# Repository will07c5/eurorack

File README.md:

This an attempt to build various basic analog synthesizer parts in the Eurorack form-factor. It is currently using clones of Curtis Electromusic ICs. Why, you might ask? Mostly just for fun and education.

The circuits are mostly based on the datasheets and various circuits around the web. In particular the triangle to sine conversion in the VCO uses part of Ray Wilson's VCO circuit.

Build at your own risk!

Note that these are currently only partially tested and working.

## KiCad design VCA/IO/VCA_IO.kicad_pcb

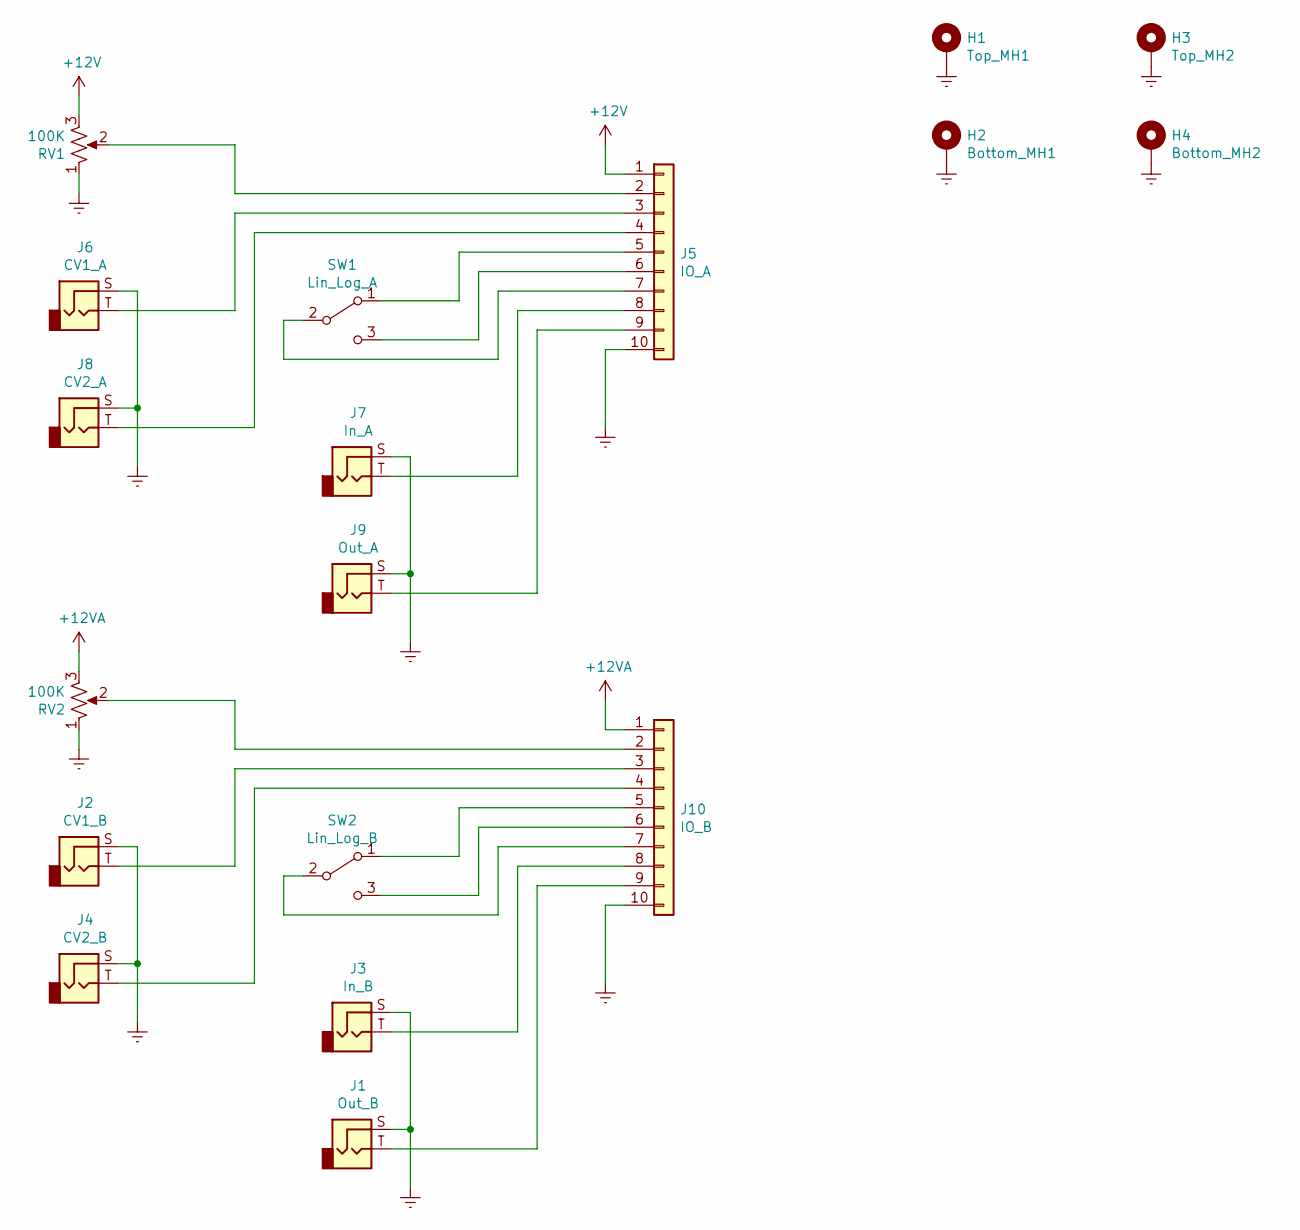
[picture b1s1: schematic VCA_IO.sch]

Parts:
H1: Top_MH1; eurorack_mounting_hole
H2: Bottom_MH1; eurorack_mounting_hole
H3: Top_MH2; eurorack_mounting_hole
H4: Bottom_MH2; eurorack_mounting_hole
J1: Out_B; Jack_3.5mm_QingPu_WQP-PJ398SM_Vertical_CircularHoles
J2: CV1_B; Jack_3.5mm_QingPu_WQP-PJ398SM_Vertical_CircularHoles
J3: In_B; Jack_3.5mm_QingPu_WQP-PJ398SM_Vertical_CircularHoles
J4: CV2_B; Jack_3.5mm_QingPu_WQP-PJ398SM_Vertical_CircularHoles
J5: IO_A; PinSocket_1x10_P2.54mm_Vertical
J6: CV1_A; Jack_3.5mm_QingPu_WQP-PJ398SM_Vertical_CircularHoles
J7: In_A; Jack_3.5mm_QingPu_WQP-PJ398SM_Vertical_CircularHoles
J8: CV2_A; Jack_3.5mm_QingPu_WQP-PJ398SM_Vertical_CircularHoles
J9: Out_A; Jack_3.5mm_QingPu_WQP-PJ398SM_Vertical_CircularHoles
J10: IO_B; PinSocket_1x10_P2.54mm_Vertical
RV1, RV2: 100K; Potentiometer_TT_P0915N
SW1: Lin_Log_A; switch
SW2: Lin_Log_B; switch

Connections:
+12V: J5.1, RV1.3
+12VA: J10.1, RV2.3
GNDREF: H1.1, H2.1, H3.1, H4.1, J1.S, J2.S, J3.S, J4.S, J5.10, J6.S, J7.S, J8.S, J9.S, J10.10, RV1.1, RV2.1
unnamed: J1.T, J10.9
unnamed: J5.2, RV1.2
unnamed: J5.3, J6.T
unnamed: J5.4, J8.T
unnamed: J5.5, SW1.1 (A)
unnamed: J5.6, SW1.3 (C)
unnamed: J5.7, SW1.2 (B)
unnamed: J5.8, J7.T
unnamed: J5.9, J9.T
unnamed: J10.2, RV2.2
unnamed: J2.T, J10.3
unnamed: J4.T, J10.4
unnamed: J10.5, SW2.1 (A)
unnamed: J10.6, SW2.3 (C)
unnamed: J10.7, SW2.2 (B)
unnamed: J3.T, J10.8

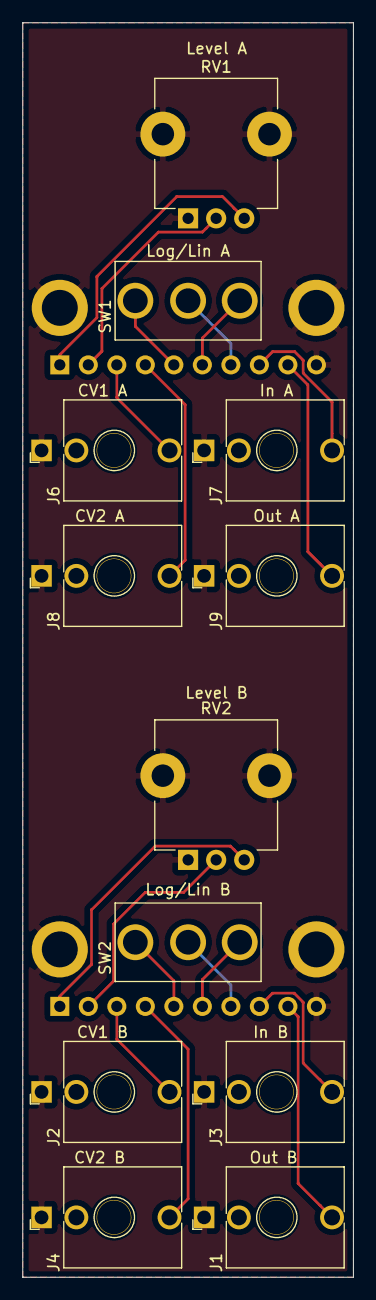
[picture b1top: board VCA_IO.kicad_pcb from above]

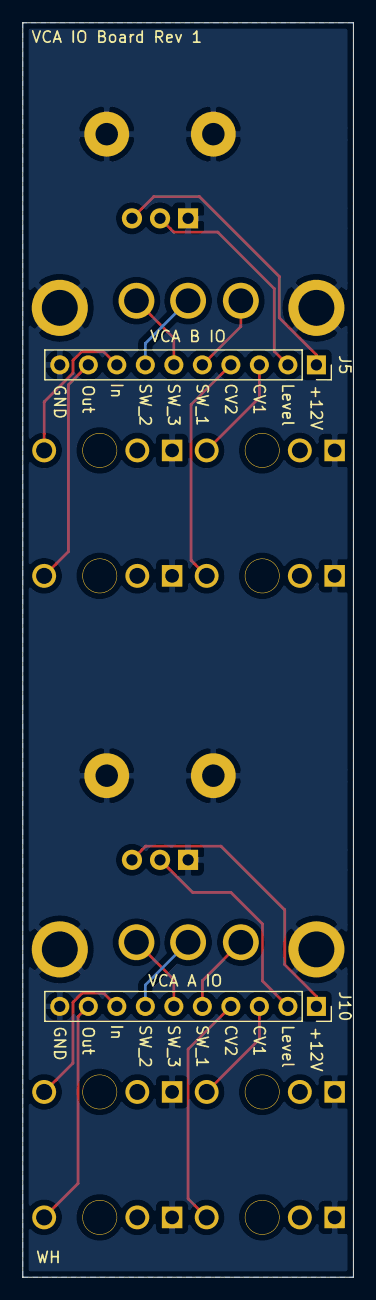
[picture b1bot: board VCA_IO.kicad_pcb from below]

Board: 2 copper layers, 29.5 x 111.8 mm, 18 parts (2 on the bottom side), 19 nets.

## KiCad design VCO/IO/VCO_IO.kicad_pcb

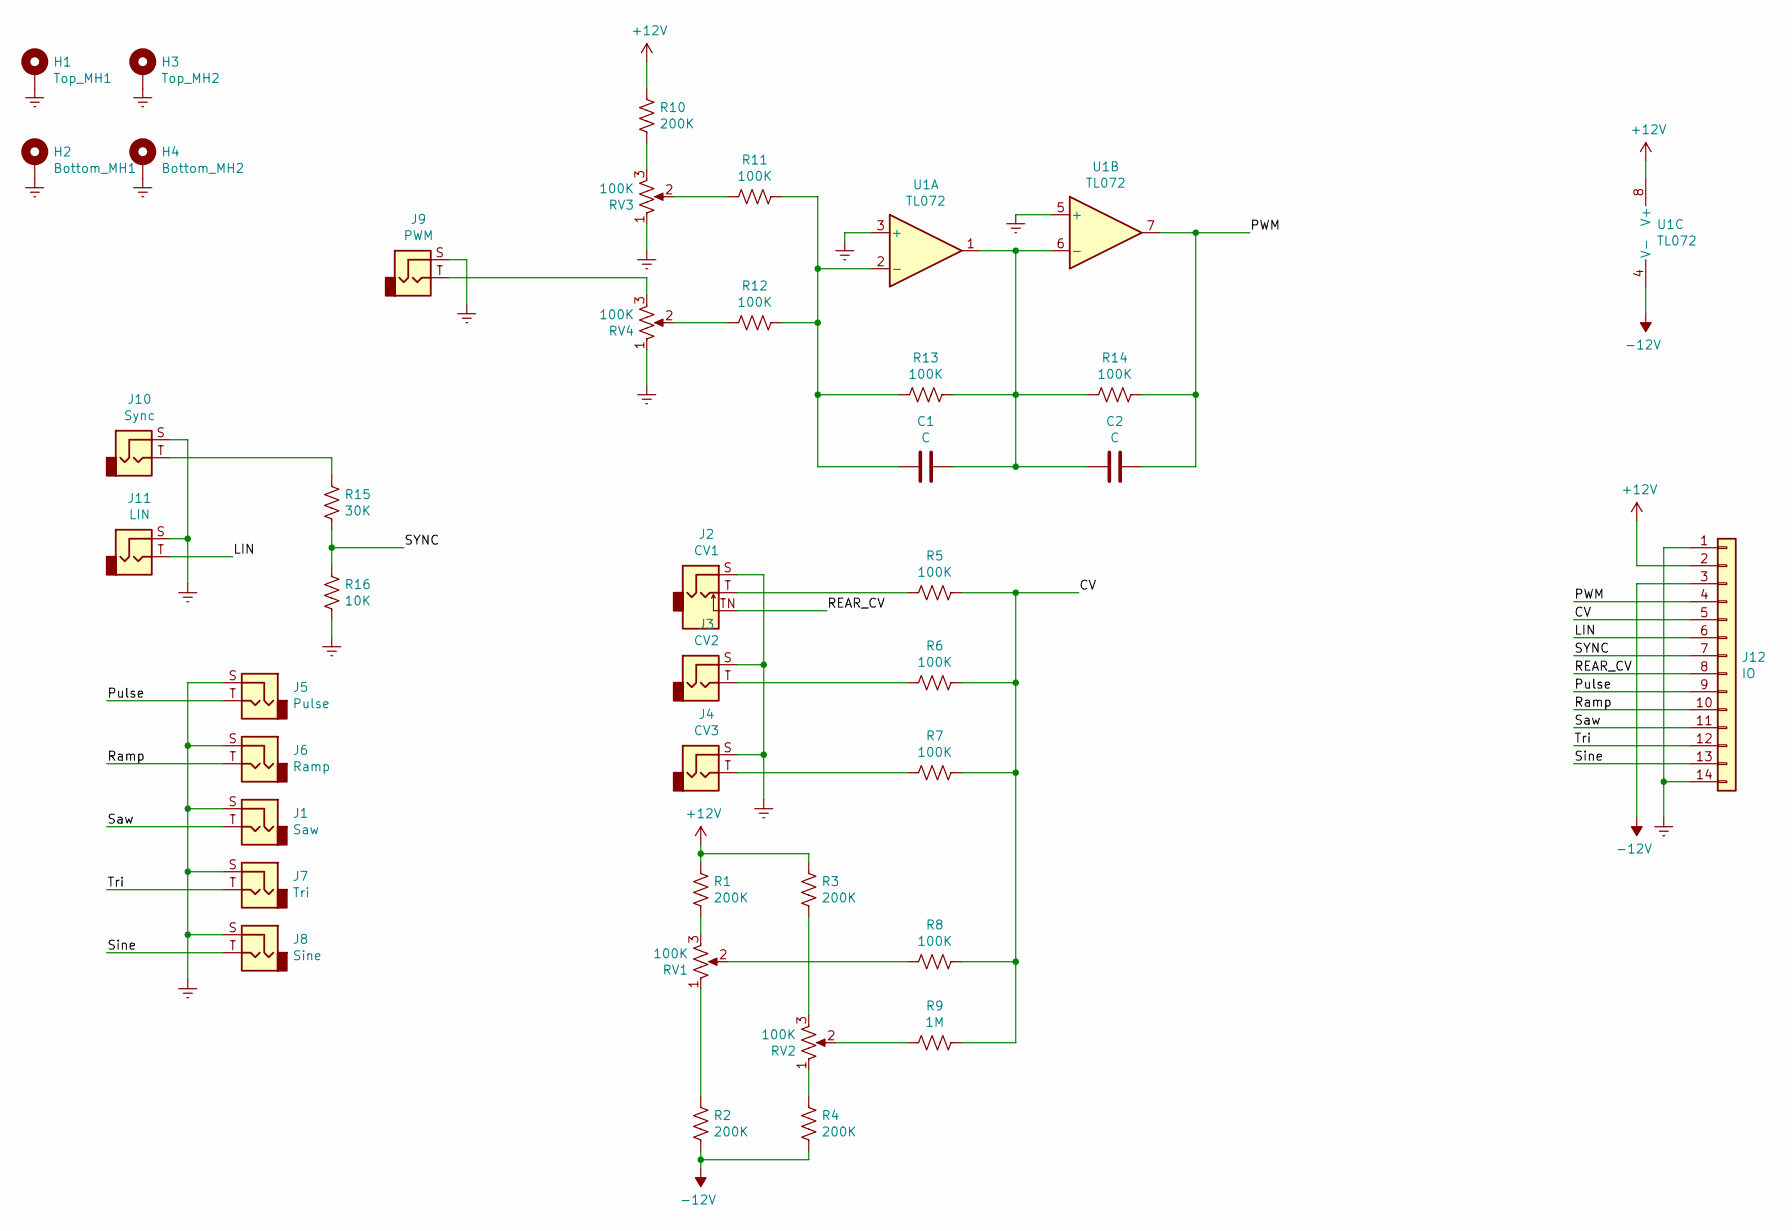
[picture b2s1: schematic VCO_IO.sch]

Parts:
C1, C2: C; C_0805_2012Metric
H1: Top_MH1; eurorack_mounting_hole
H2: Bottom_MH1; eurorack_mounting_hole
H3: Top_MH2; eurorack_mounting_hole
H4: Bottom_MH2; eurorack_mounting_hole
J1: Saw; Jack_3.5mm_QingPu_WQP-PJ398SM_Vertical_CircularHoles
J2: CV1; Jack_3.5mm_QingPu_WQP-PJ398SM_Vertical_CircularHoles
J3: CV2; Jack_3.5mm_QingPu_WQP-PJ398SM_Vertical_CircularHoles
J4: CV3; Jack_3.5mm_QingPu_WQP-PJ398SM_Vertical_CircularHoles
J5: Pulse; Jack_3.5mm_QingPu_WQP-PJ398SM_Vertical_CircularHoles
J6: Ramp; Jack_3.5mm_QingPu_WQP-PJ398SM_Vertical_CircularHoles
J7: Tri; Jack_3.5mm_QingPu_WQP-PJ398SM_Vertical_CircularHoles
J8: Sine; Jack_3.5mm_QingPu_WQP-PJ398SM_Vertical_CircularHoles
J9: PWM; Jack_3.5mm_QingPu_WQP-PJ398SM_Vertical_CircularHoles
J10: Sync; Jack_3.5mm_QingPu_WQP-PJ398SM_Vertical_CircularHoles
J11: LIN; Jack_3.5mm_QingPu_WQP-PJ398SM_Vertical_CircularHoles
J12: IO; PinSocket_1x14_P2.54mm_Vertical
R1, R2, R3, R4, R10: 200K; R_0805_2012Metric
R5, R6, R7, R8, R11, R12, R13, R14: 100K; R_0805_2012Metric
R9: 1M; R_0805_2012Metric
R15: 30K; R_0805_2012Metric
R16: 10K; R_0805_2012Metric
RV1, RV2, RV3, RV4: 100K; Potentiometer_TT_P0915N
U1: TL072; DIP-8_W7.62mm

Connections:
+12V: J12.2, R1.1, R3.1, R10.1, U1.8 (V+)
-12V: J12.3, R2.2, R4.2, U1.4 (V-)
/CV: J12.5, R5.1, R6.1, R7.1, R8.1, R9.1
/LIN: J11.T, J12.6
/PWM: C2.1, J12.4, R14.1, U1.7
/Pulse: J5.T, J12.9
/REAR_CV: J2.TN, J12.8
/Ramp: J6.T, J12.10
/SYNC: J12.7, R15.2, R16.1
/Saw: J1.T, J12.11
/Sine: J8.T, J12.13
/Tri: J7.T, J12.12
GNDREF: H1.1, H2.1, H3.1, H4.1, J1.S, J2.S, J3.S, J4.S, J5.S, J6.S, J7.S, J8.S, J9.S, J10.S, J11.S, J12.1, J12.14, R16.2, RV3.1, RV4.1, U1.3 (+), U1.5 (+)
unnamed: C1.1, C2.2, R13.1, R14.2, U1.1, U1.6 (-)
unnamed: C1.2, R11.1, R12.1, R13.2, U1.2 (-)
unnamed: J2.T, R5.2
unnamed: J3.T, R6.2
unnamed: J4.T, R7.2
unnamed: J9.T, RV4.3
unnamed: J10.T, R15.1
unnamed: R1.2, RV1.3
unnamed: R2.1, RV1.1
unnamed: R3.2, RV2.3
unnamed: R4.1, RV2.1
unnamed: R8.2, RV1.2
unnamed: R9.2, RV2.2
unnamed: R10.2, RV3.3
unnamed: R11.2, RV3.2
unnamed: R12.2, RV4.2

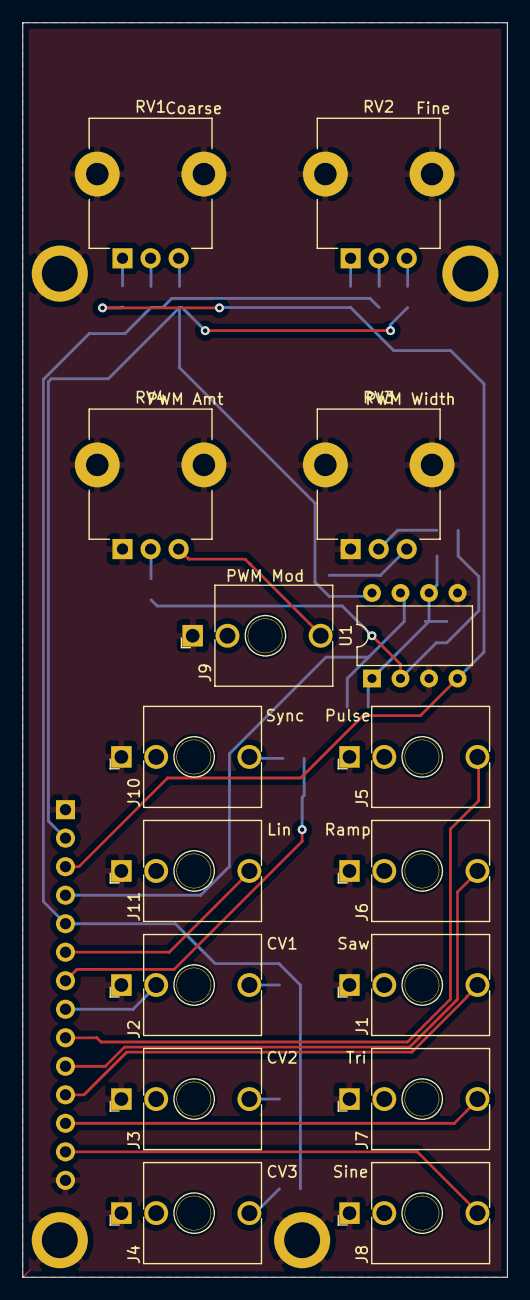
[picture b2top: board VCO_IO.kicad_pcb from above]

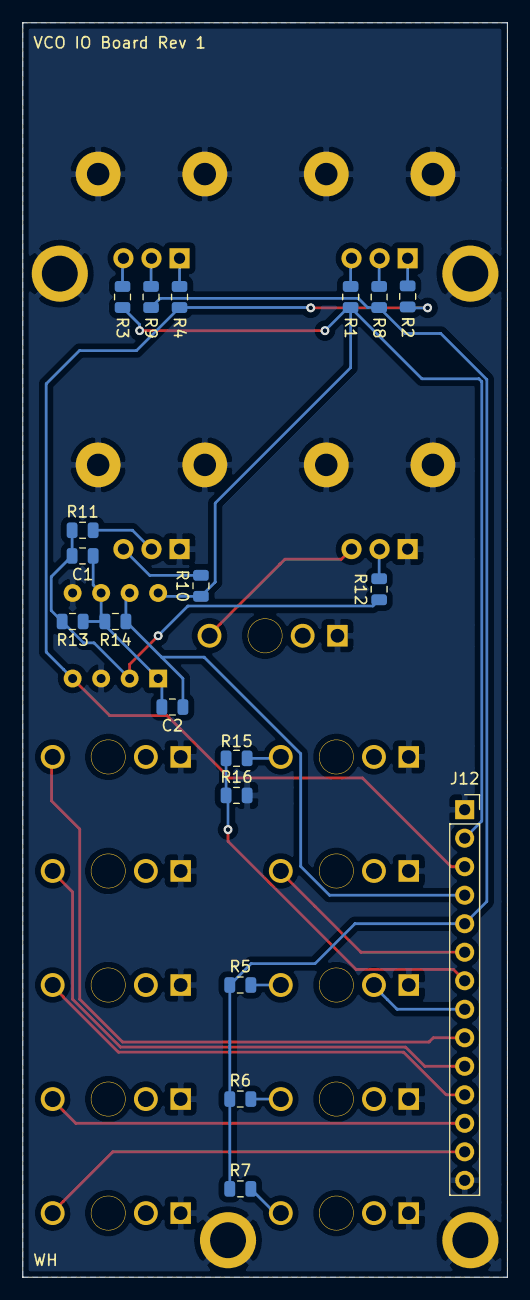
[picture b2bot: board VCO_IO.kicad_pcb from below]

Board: 2 copper layers, 43.2 x 111.8 mm, 39 parts (19 on the bottom side), 29 nets.

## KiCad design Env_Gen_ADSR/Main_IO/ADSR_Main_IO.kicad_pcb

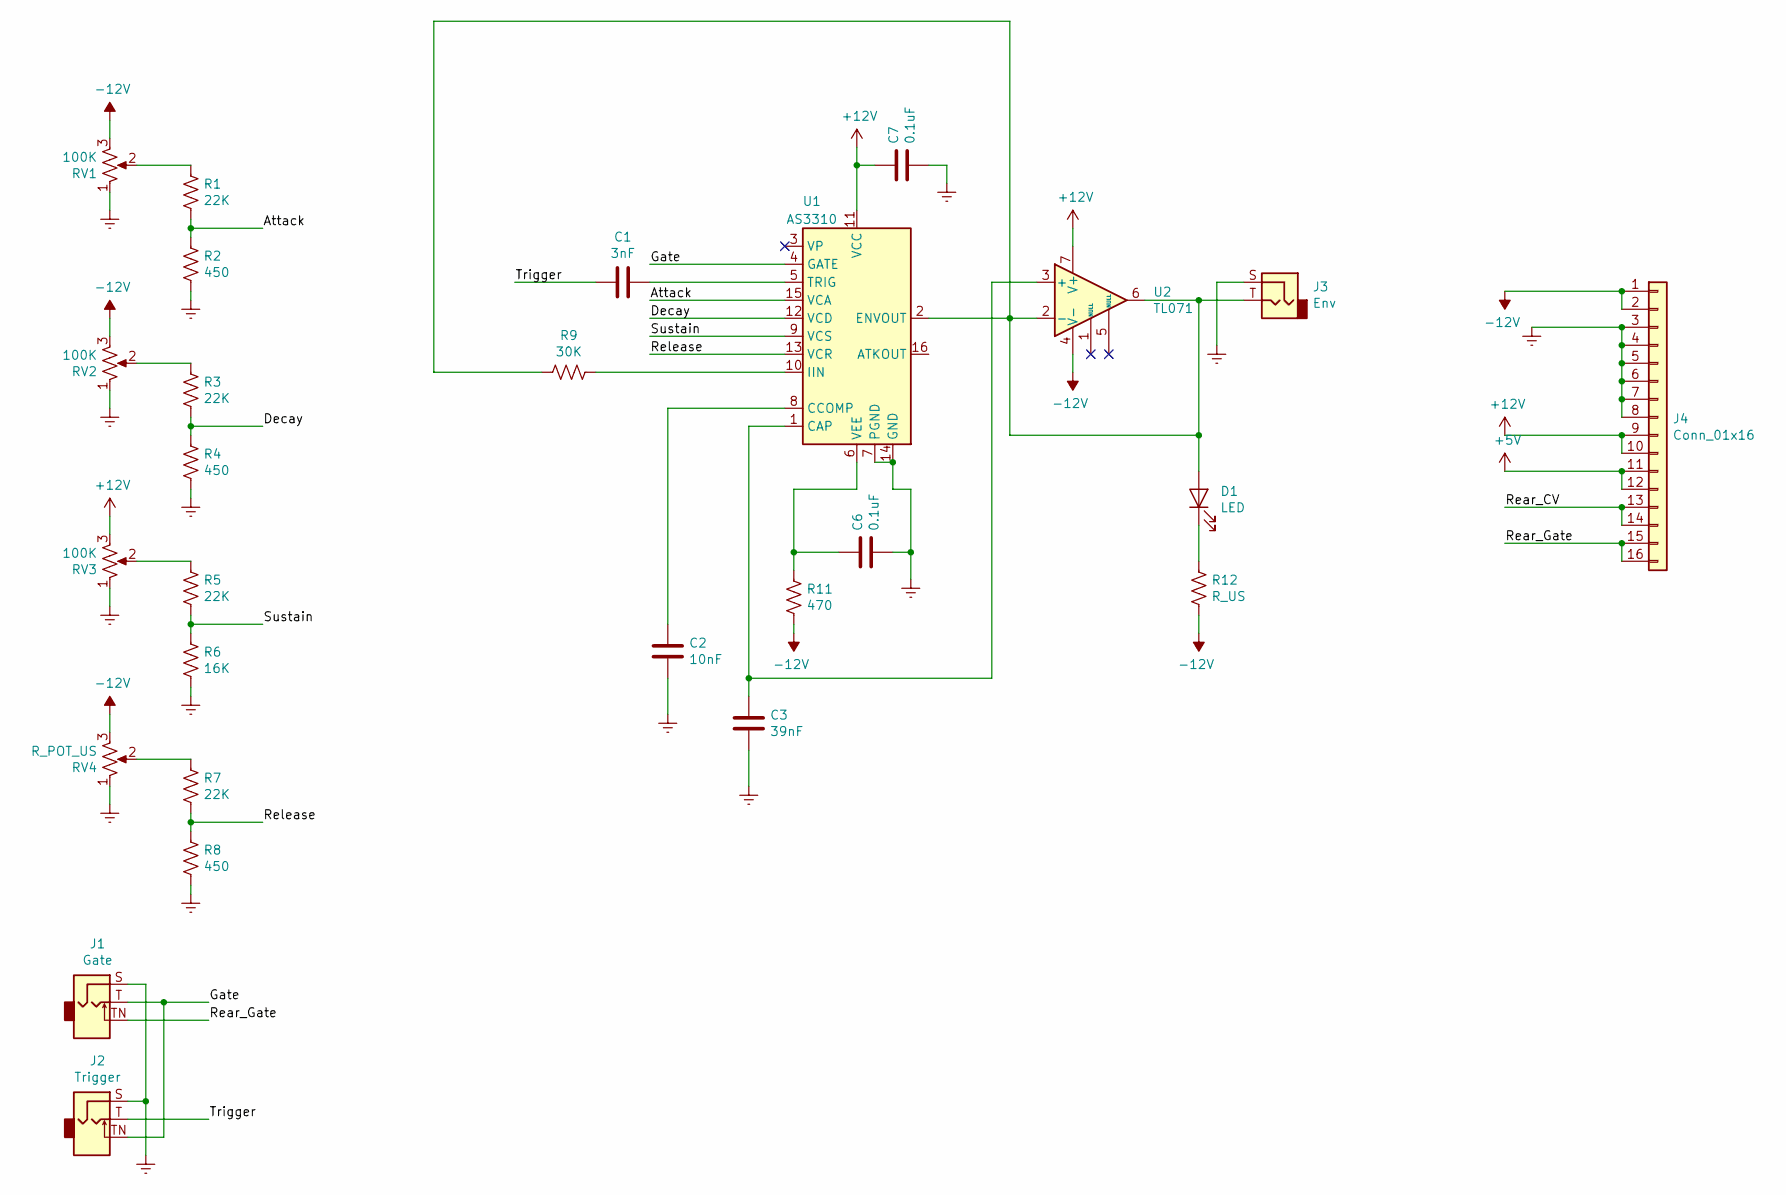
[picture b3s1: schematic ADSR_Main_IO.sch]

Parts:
C1: 3nF; C_0805_2012Metric
C2: 10nF; C_0805_2012Metric
C3: 39nF; C_0805_2012Metric
C6, C7: 0.1uF; C_0805_2012Metric
D1: LED; LED_D5.0mm
J1: Gate; Jack_3.5mm_QingPu_WQP-PJ398SM_Vertical_CircularHoles
J2: Trigger; Jack_3.5mm_QingPu_WQP-PJ398SM_Vertical_CircularHoles
J3: Env; Jack_3.5mm_QingPu_WQP-PJ398SM_Vertical_CircularHoles
J4: Conn_01x16; IDC-Header_2x08_P2.54mm_Vertical
R1, R3, R5, R7: 22K; R_0805_2012Metric
R2, R4, R8: 450; R_0805_2012Metric
R6: 16K; R_0805_2012Metric
R9: 30K; R_0805_2012Metric
R11: 470; R_0805_2012Metric
R12: R_US; R_0805_2012Metric
RV1, RV2, RV3: 100K; Potentiometer_TT_P0915N
RV4: R_POT_US; Potentiometer_TT_P0915N
U1: AS3310; DIP-16_W7.62mm
U2: TL071; DIP-8_W7.62mm

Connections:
+5V: J4.11, J4.12
+12V: C7.1, J4.9, J4.10, RV3.3, U1.11 (VCC), U2.7 (V+)
-12V: J4.1, J4.2, R11.2, R12.2, RV1.3, RV2.3, RV4.3, U2.4 (V-)
/Attack: R1.2, R2.1, U1.15 (VCA)
/Decay: R3.2, R4.1, U1.12 (VCD)
/Gate: J1.T, J2.TN, U1.4 (GATE)
/Rear_CV: J4.13, J4.14
/Rear_Gate: J1.TN, J4.15, J4.16
/Release: R7.2, R8.1, U1.13 (VCR)
/Sustain: R5.2, R6.1, U1.9 (VCS)
/Trigger: C1.2, J2.T
GNDREF: C2.2, C3.2, C6.2, C7.2, J1.S, J2.S, J3.S, J4.3, J4.4, J4.5, J4.6, J4.7, J4.8, R2.2, R4.2, R6.2, R8.2, RV1.1, RV2.1, RV3.1, RV4.1, U1.7 (PGND), U1.14 (GND)
unnamed: C1.1, U1.5 (TRIG)
unnamed: C2.1, U1.8 (CCOMP)
unnamed: C3.1, U1.1 (CAP), U2.3 (+)
unnamed: C6.1, R11.1, U1.6 (VEE)
unnamed: D1.1 (K), R12.1
unnamed: D1.2 (A), J3.T, R9.2, U1.2 (ENVOUT), U2.2 (-), U2.6
unnamed: R1.1, RV1.2
unnamed: R3.1, RV2.2
unnamed: R5.1, RV3.2
unnamed: R7.1, RV4.2
unnamed: R9.1, U1.10 (IIN)

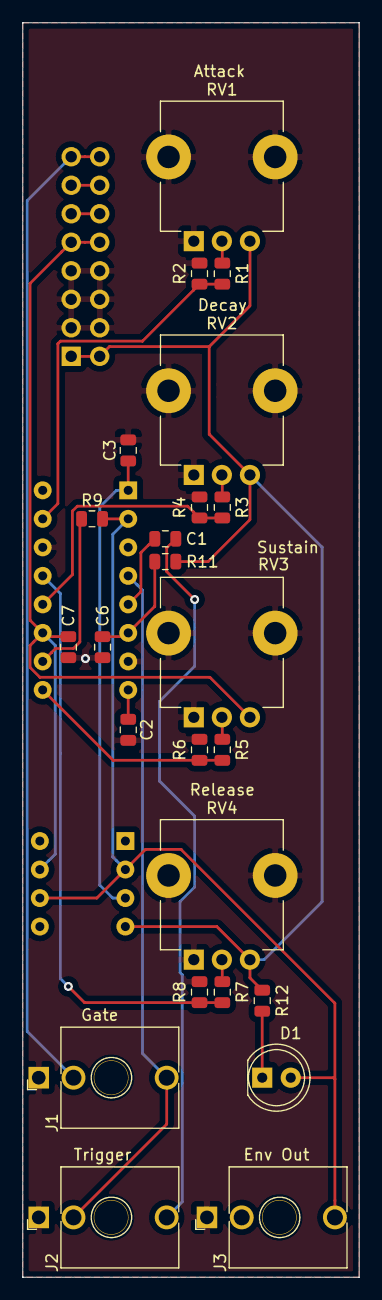
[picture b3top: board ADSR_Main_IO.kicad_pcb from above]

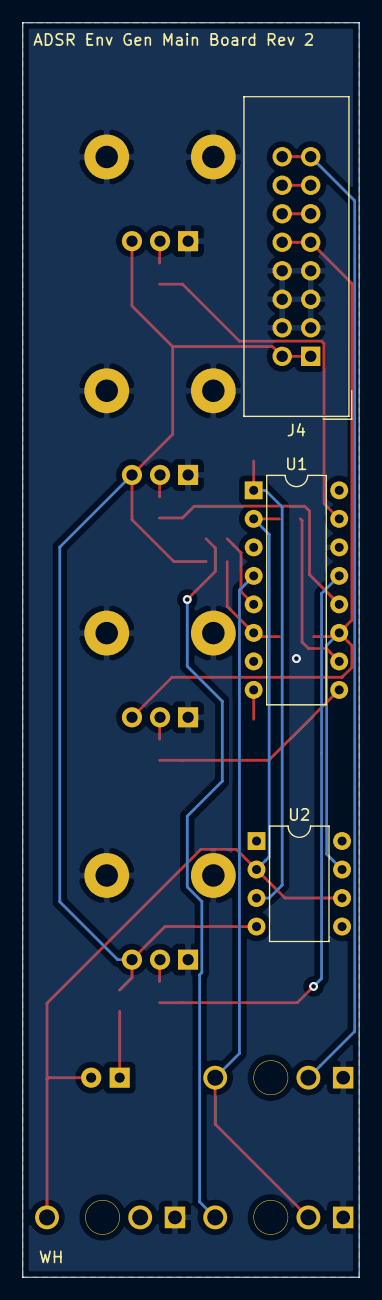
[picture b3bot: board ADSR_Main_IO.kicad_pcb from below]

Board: 2 copper layers, 30.0 x 111.8 mm, 27 parts (3 on the bottom side), 23 nets.

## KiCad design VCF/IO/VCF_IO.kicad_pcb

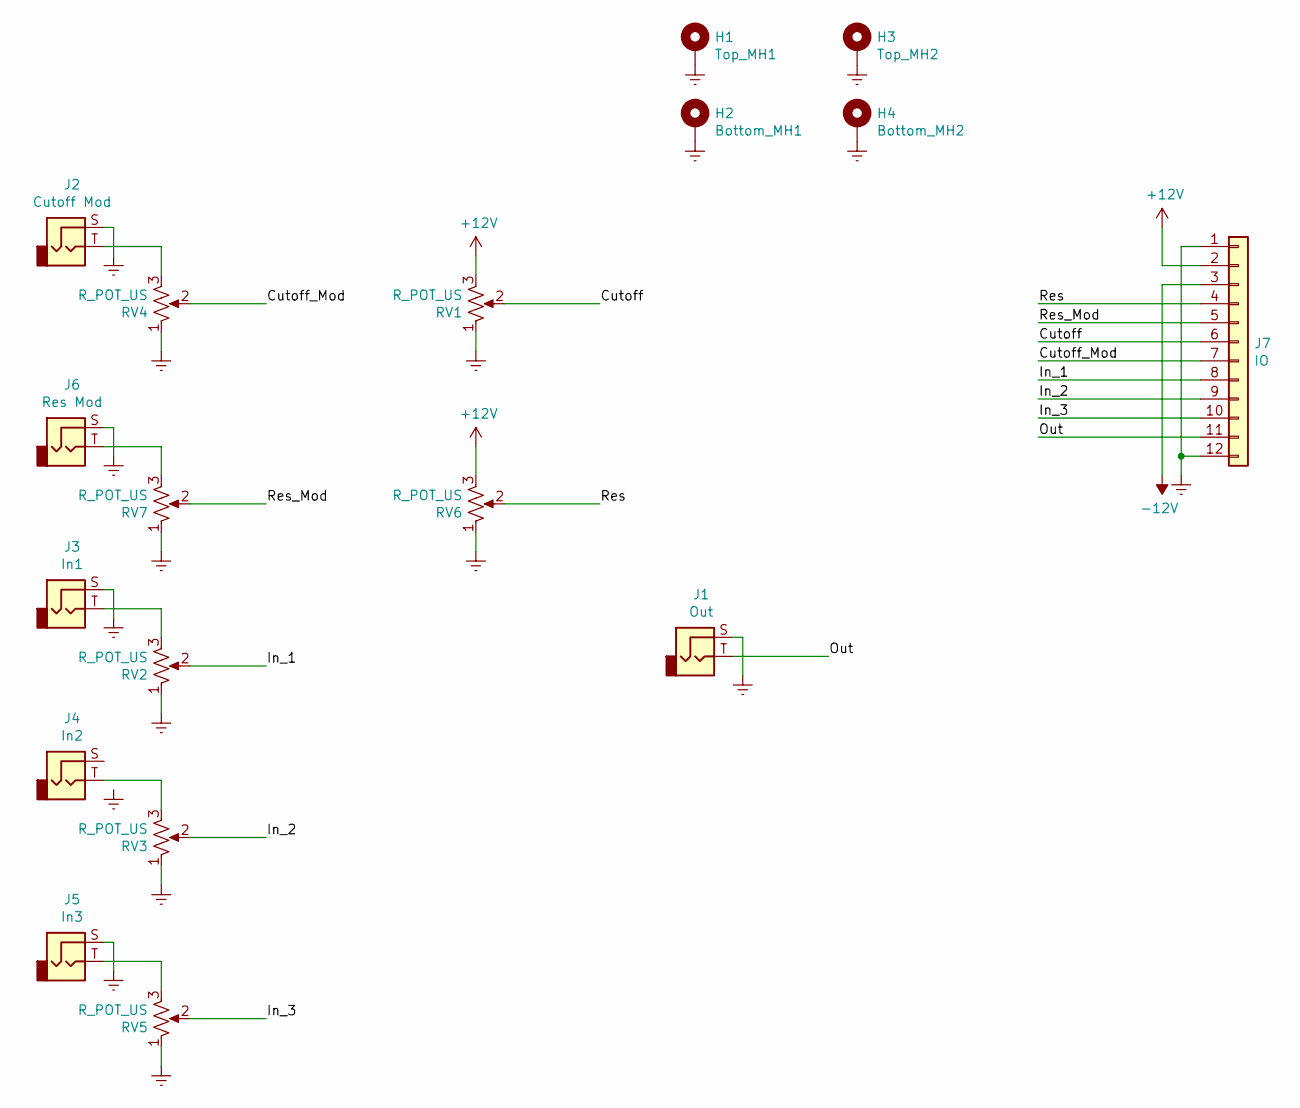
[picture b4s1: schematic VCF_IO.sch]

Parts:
H1: Top_MH1; eurorack_mounting_hole
H2: Bottom_MH1; eurorack_mounting_hole
H3: Top_MH2; eurorack_mounting_hole
H4: Bottom_MH2; eurorack_mounting_hole
J1: Out; Jack_3.5mm_QingPu_WQP-PJ398SM_Vertical_CircularHoles
J2: Cutoff Mod; Jack_3.5mm_QingPu_WQP-PJ398SM_Vertical_CircularHoles
J3: In1; Jack_3.5mm_QingPu_WQP-PJ398SM_Vertical_CircularHoles
J4: In2; Jack_3.5mm_QingPu_WQP-PJ398SM_Vertical_CircularHoles
J5: In3; Jack_3.5mm_QingPu_WQP-PJ398SM_Vertical_CircularHoles
J6: Res Mod; Jack_3.5mm_QingPu_WQP-PJ398SM_Vertical_CircularHoles
J7: IO; PinSocket_1x12_P2.54mm_Vertical
RV1, RV2, RV3, RV4, RV5, RV6, RV7: R_POT_US; Potentiometer_TT_P0915N

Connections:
+12V: J7.2, RV1.3, RV6.3
-12V: J7.3
/Cutoff: J7.6, RV1.2
/Cutoff_Mod: J7.7, RV4.2
/In_1: J7.8, RV2.2
/In_2: J7.9, RV3.2
/In_3: J7.10, RV5.2
/Out: J1.T, J7.11
/Res: J7.4, RV6.2
/Res_Mod: J7.5, RV7.2
GNDREF: H1.1, H2.1, H3.1, H4.1, J1.S, J2.S, J3.S, J5.S, J6.S, J7.1, J7.12, RV1.1, RV2.1, RV3.1, RV4.1, RV5.1, RV6.1, RV7.1
unnamed: J2.T, RV4.3
unnamed: J3.T, RV2.3
unnamed: J4.T, RV3.3
unnamed: J5.T, RV5.3
unnamed: J6.T, RV7.3

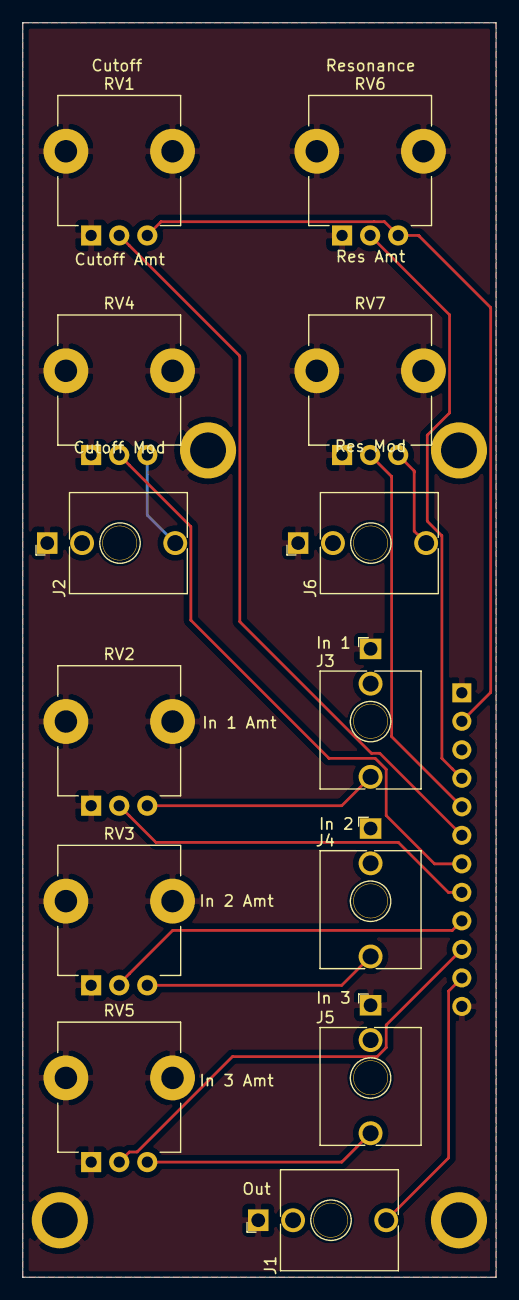
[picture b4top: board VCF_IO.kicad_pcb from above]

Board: 2 copper layers, 42.2 x 111.8 mm, 18 parts (1 on the bottom side), 15 nets.

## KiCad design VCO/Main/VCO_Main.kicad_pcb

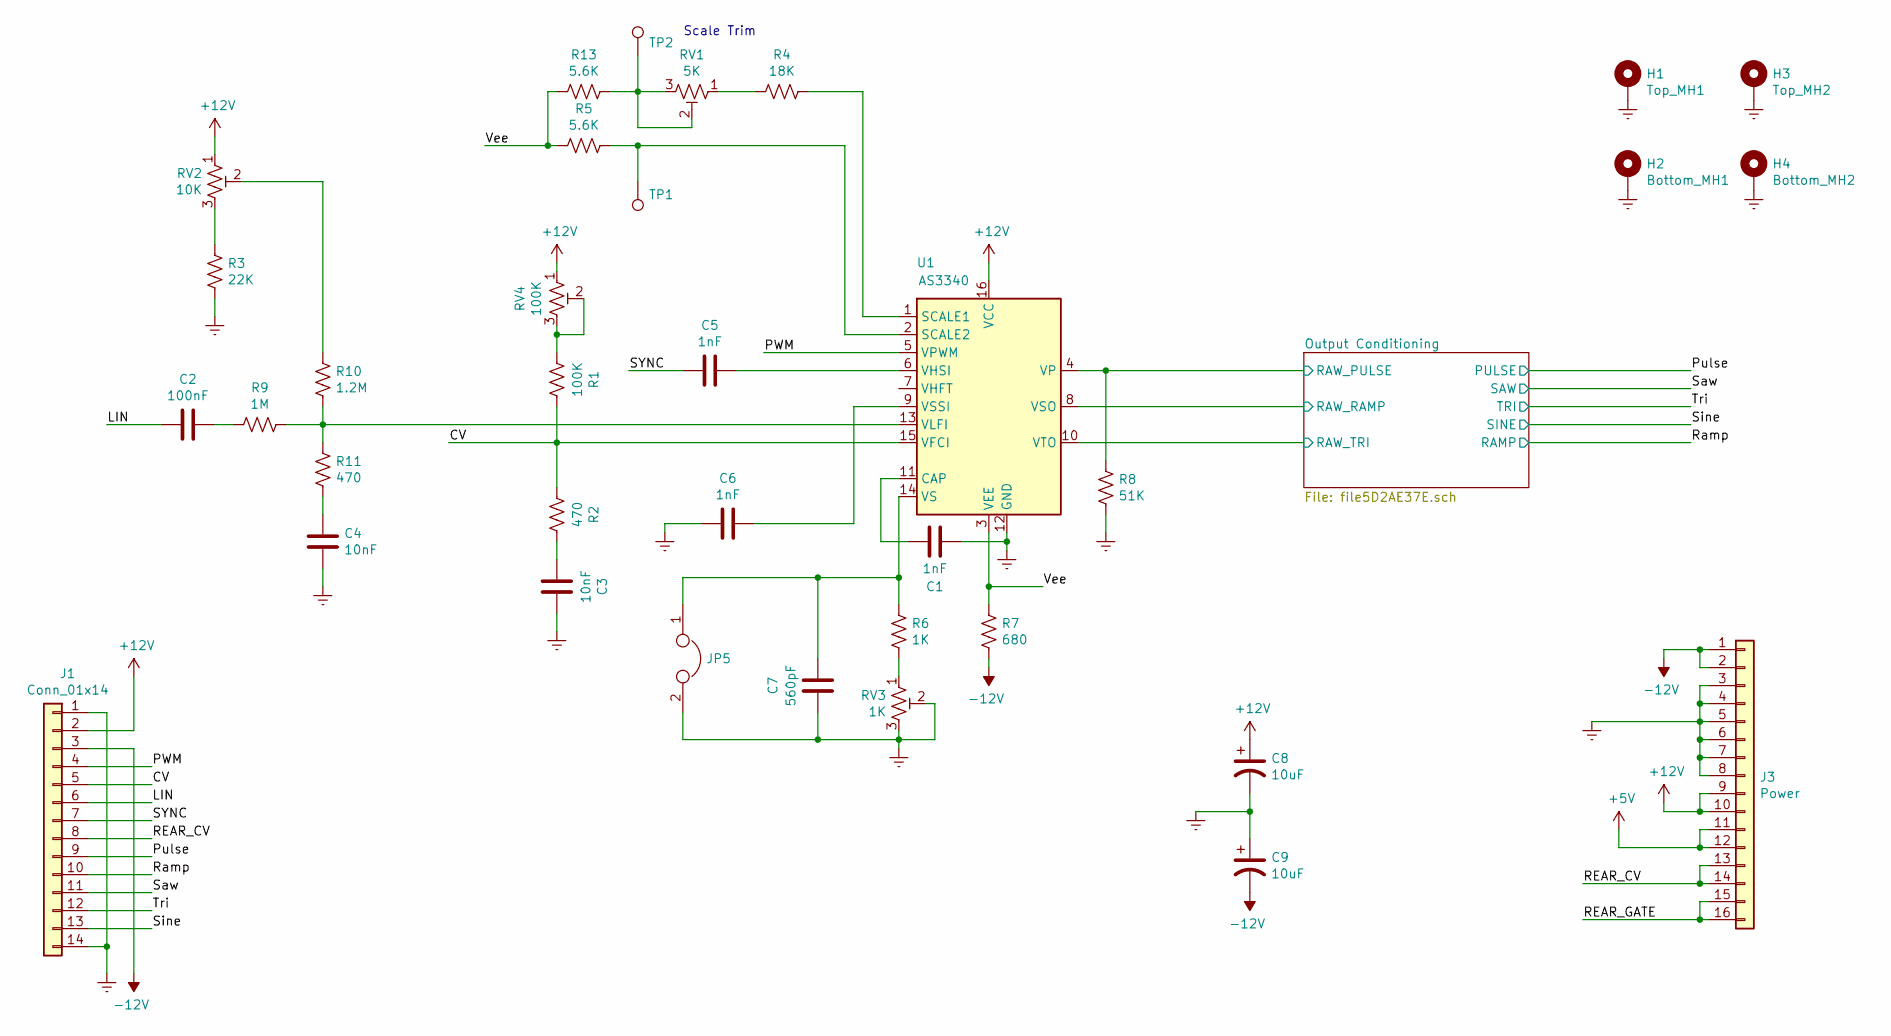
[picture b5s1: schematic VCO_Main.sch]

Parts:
C1: 1nF; Mica_Cap
C2: 100nF; C_0805_2012Metric
C3, C4: 10nF; C_0805_2012Metric
C5, C6: 1nF; C_0805_2012Metric
C7: 560pF; C_0805_2012Metric
C8, C9: 10uF; CP_Elec_4x3
H1: Top_MH1; eurorack_mounting_hole
H2: Bottom_MH1; eurorack_mounting_hole
H3: Top_MH2; eurorack_mounting_hole
H4: Bottom_MH2; eurorack_mounting_hole
J1: Conn_01x14; PinHeader_1x14_P2.54mm_Vertical
J3: Power; IDC-Header_2x08_P2.54mm_Vertical
JP5: Jumper; PinHeader_1x02_P2.54mm_Vertical
R1: 100K; R_0805_2012Metric
R2, R11: 470; R_0805_2012Metric
R3: 22K; R_0805_2012Metric
R4: 18K; R_0805_2012Metric
R5, R13: 5.6K; R_0805_2012Metric
R6: 1K; R_0805_2012Metric
R7: 680; R_0805_2012Metric
R8: 51K; R_0805_2012Metric
R9: 1M; R_0805_2012Metric
R10: 1.2M; R_0805_2012Metric
RV1: 5K; Potentiometer_Bourns_3296W_Vertical
RV2: 10K; Potentiometer_Bourns_3296W_Vertical
RV3: 1K; Potentiometer_Bourns_3296W_Vertical
RV4: 100K; Potentiometer_Bourns_3296W_Vertical
TP1, TP2: TestPoint; TestPoint_Pad_D2.0mm
U1: AS3340; DIP-16_W7.62mm

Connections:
+5V: J3.11, J3.12
+12V: C8.1, J1.2, J3.9, J3.10, RV2.1, RV4.1, U1.16 (VCC); also elsewhere on the board
-12V: C9.2, J1.3, J3.1, J3.2, R7.2; also elsewhere on the board
/CV: J1.5, R1.1, R2.2, U1.15 (VFCI)
/LIN: C2.2, J1.6
/Output Conditioning/RAW_PULSE: R8.2, U1.4 (VP); also elsewhere on the board
/Output Conditioning/RAW_RAMP: U1.8 (VSO); also elsewhere on the board
/Output Conditioning/RAW_TRI: U1.10 (VTO); also elsewhere on the board
/PWM: J1.4, U1.5 (VPWM)
/Pulse: J1.9; also elsewhere on the board
/REAR_CV: J1.8, J3.13, J3.14
/REAR_GATE: J3.15, J3.16
/Ramp: J1.10; also elsewhere on the board
/SYNC: C5.2, J1.7
/Saw: J1.11; also elsewhere on the board
/Sine: J1.13; also elsewhere on the board
/Tri: J1.12; also elsewhere on the board
/Vee: R5.1, R7.1, R13.1, U1.3 (VEE)
GNDREF: C1.1, C3.1, C4.1, C6.2, C7.1, C8.2, C9.1, H1.1, H2.1, H3.1, H4.1, J1.1, J1.14, J3.3, J3.4, J3.5, J3.6, J3.7, J3.8, JP5.2, R3.1, R8.1, RV3.2, RV3.3, U1.12 (GND); also elsewhere on the board
unnamed: C1.2, U1.11 (CAP)
unnamed: C2.1, R9.2
unnamed: C3.2, R2.1
unnamed: C4.2, R11.1
unnamed: C5.1, U1.6 (VHSI)
unnamed: C6.1, U1.9 (VSSI)
unnamed: C7.2, JP5.1, R6.2, U1.14 (VS)
unnamed: R1.2, RV4.2, RV4.3
unnamed: R3.2, RV2.3
unnamed: R4.1, RV1.1
unnamed: R4.2, U1.1 (SCALE1)
unnamed: R5.2, TP1.1, U1.2 (SCALE2)
unnamed: R6.1, RV3.1
unnamed: R9.1, R10.1, R11.2, U1.13 (VLFI)
unnamed: R10.2, RV2.2
unnamed: R13.2, RV1.2, RV1.3, TP2.1

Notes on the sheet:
Scale Trim

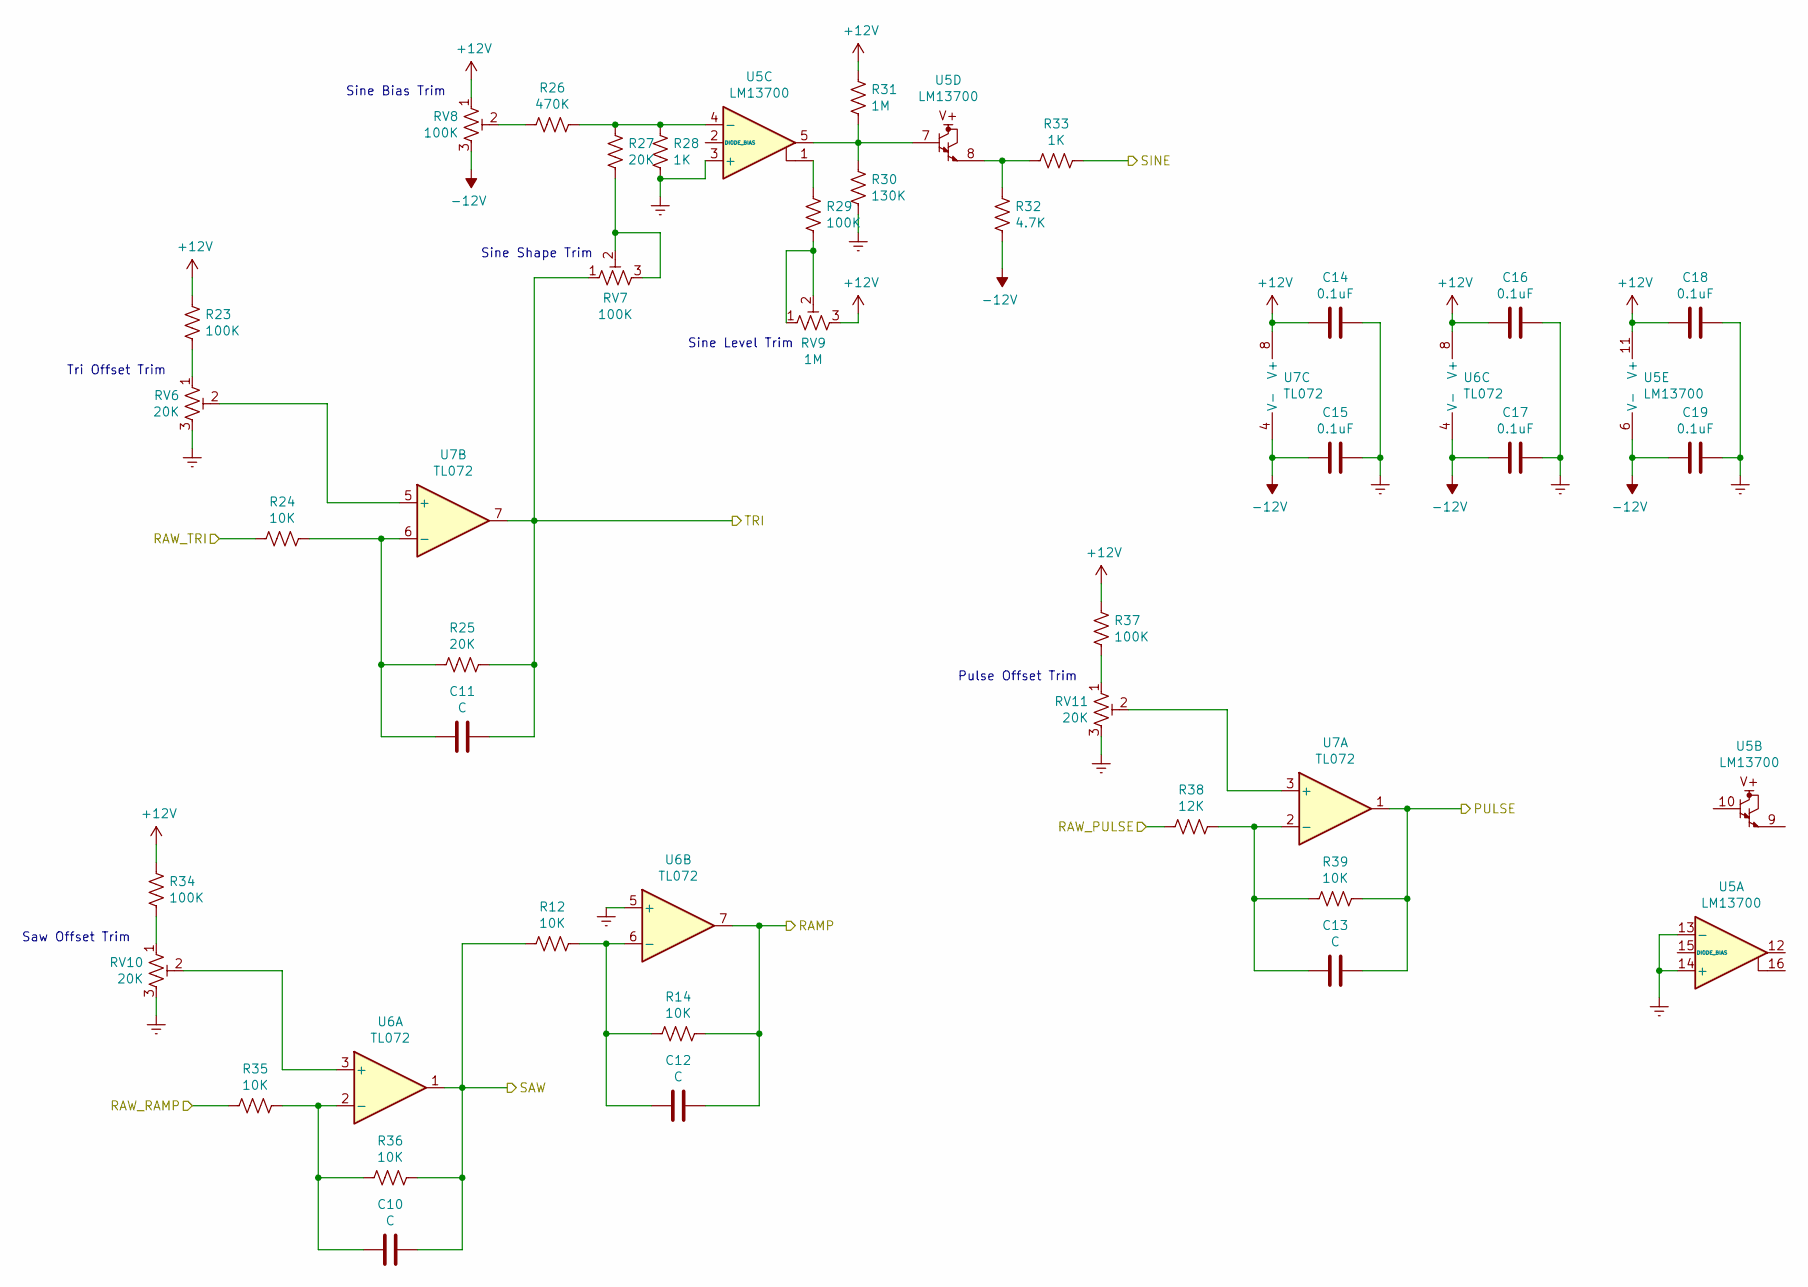
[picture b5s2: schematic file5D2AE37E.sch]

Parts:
C10, C11, C12, C13: C; C_0805_2012Metric
C14, C15, C16, C17, C18, C19: 0.1uF; C_0805_2012Metric
R12, R14, R24, R35, R36, R39: 10K; R_0805_2012Metric
R23, R29, R34, R37: 100K; R_0805_2012Metric
R25, R27: 20K; R_0805_2012Metric
R26: 470K; R_0805_2012Metric
R28, R33: 1K; R_0805_2012Metric
R30: 130K; R_0805_2012Metric
R31: 1M; R_0805_2012Metric
R32: 4.7K; R_0805_2012Metric
R38: 12K; R_0805_2012Metric
RV6, RV10, RV11: 20K; Potentiometer_Bourns_3296W_Vertical
RV7, RV8: 100K; Potentiometer_Bourns_3296W_Vertical
RV9: 1M; Potentiometer_Bourns_3296W_Vertical
U5: LM13700; DIP-16_W7.62mm
U6, U7: TL072; DIP-8_W7.62mm

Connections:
+12V: C14.2, C16.2, C18.2, R23.1, R31.1, R34.1, R37.1, RV8.1, RV9.3, U5.11 (V+), U6.8 (V+), U7.8 (V+); also elsewhere on the board
-12V: C15.2, C17.2, C19.2, R32.2, RV8.3, U5.6 (V-), U6.4 (V-), U7.4 (V-); also elsewhere on the board
/Output Conditioning/RAW_PULSE: R38.1; also elsewhere on the board
/Output Conditioning/RAW_RAMP: R35.1; also elsewhere on the board
/Output Conditioning/RAW_TRI: R24.1; also elsewhere on the board
/Pulse: C13.1, R39.2, U7.1; also elsewhere on the board
/Ramp: C12.1, R14.2, U6.7; also elsewhere on the board
/Saw: C10.1, R12.1, R36.2, U6.1; also elsewhere on the board
/Sine: R33.2; also elsewhere on the board
/Tri: C11.1, R25.2, RV7.1, U7.7; also elsewhere on the board
GNDREF: C14.1, C15.1, C16.1, C17.1, C18.1, C19.1, R28.2, R30.2, RV6.3, RV10.3, RV11.3, U5.3 (+), U5.13 (-), U5.14 (+), U6.5 (+); also elsewhere on the board
unnamed: C10.2, R35.2, R36.1, U6.2 (-)
unnamed: C11.2, R24.2, R25.1, U7.6 (-)
unnamed: C12.2, R12.2, R14.1, U6.6 (-)
unnamed: C13.2, R38.2, R39.1, U7.2 (-)
unnamed: R23.2, RV6.1
unnamed: R26.1, RV8.2
unnamed: R26.2, R27.1, R28.1, U5.4 (-)
unnamed: R27.2, RV7.2, RV7.3
unnamed: R29.1, U5.1
unnamed: R29.2, RV9.1, RV9.2
unnamed: R30.1, R31.2, U5.5, U5.7
unnamed: R32.1, R33.1, U5.8
unnamed: R34.2, RV10.1
unnamed: R37.2, RV11.1
unnamed: RV6.2, U7.5 (+)
unnamed: RV10.2, U6.3 (+)
unnamed: RV11.2, U7.3 (+)

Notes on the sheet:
Tri Offset Trim
Sine Bias Trim
Sine Shape Trim
Sine Level Trim
Saw Offset Trim
Pulse Offset Trim
